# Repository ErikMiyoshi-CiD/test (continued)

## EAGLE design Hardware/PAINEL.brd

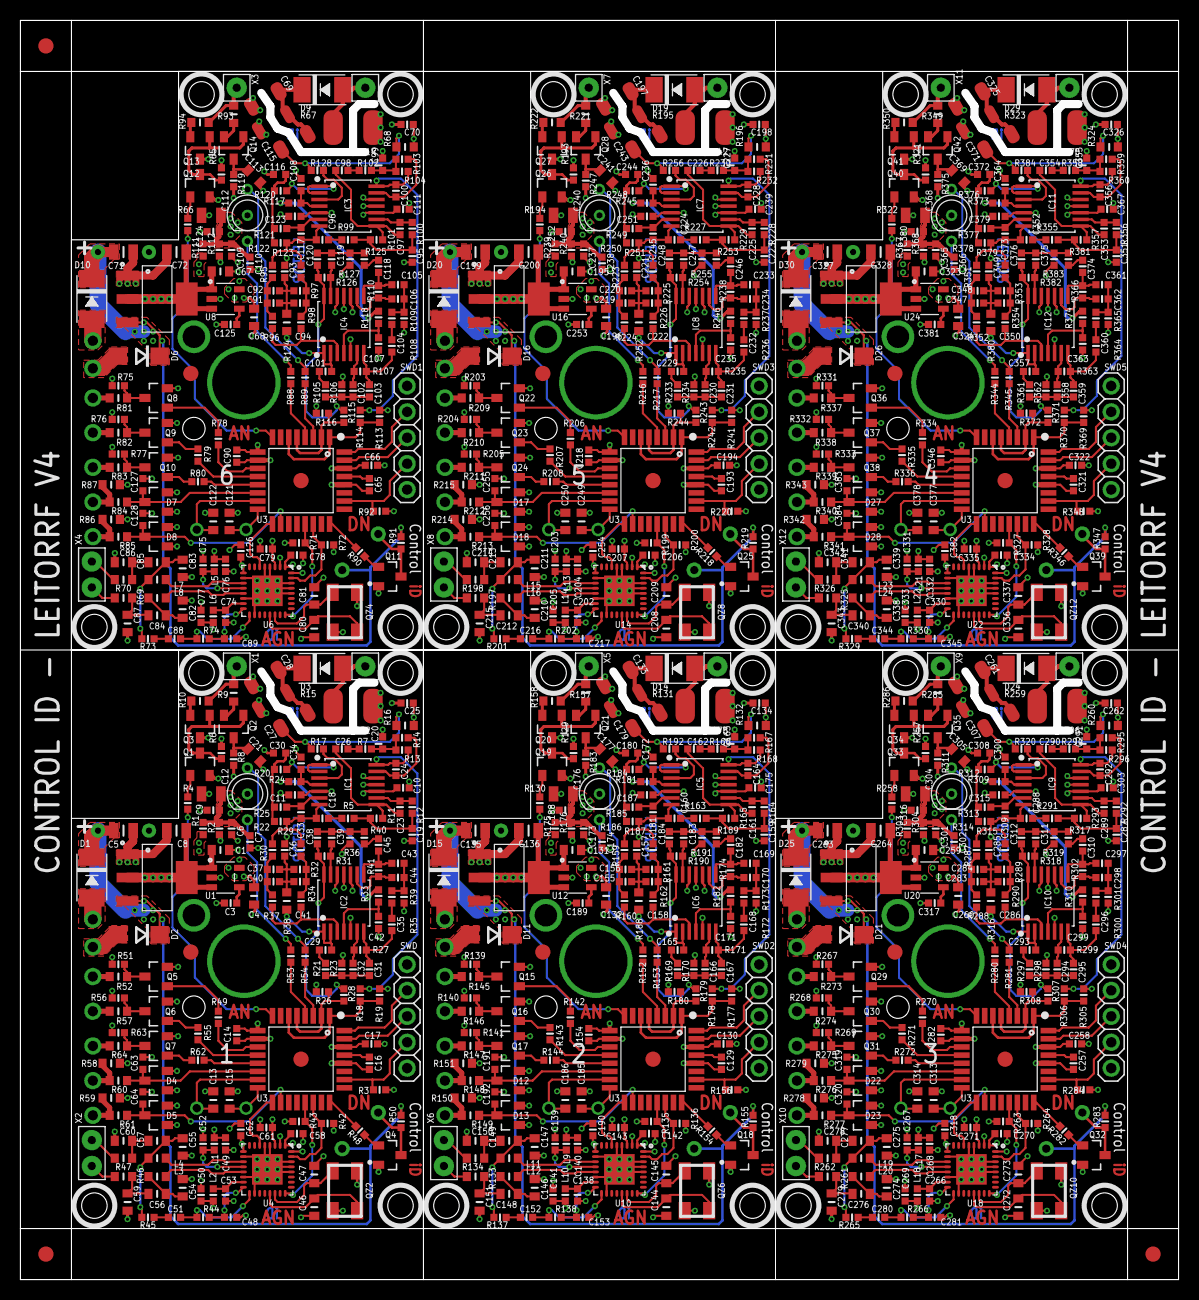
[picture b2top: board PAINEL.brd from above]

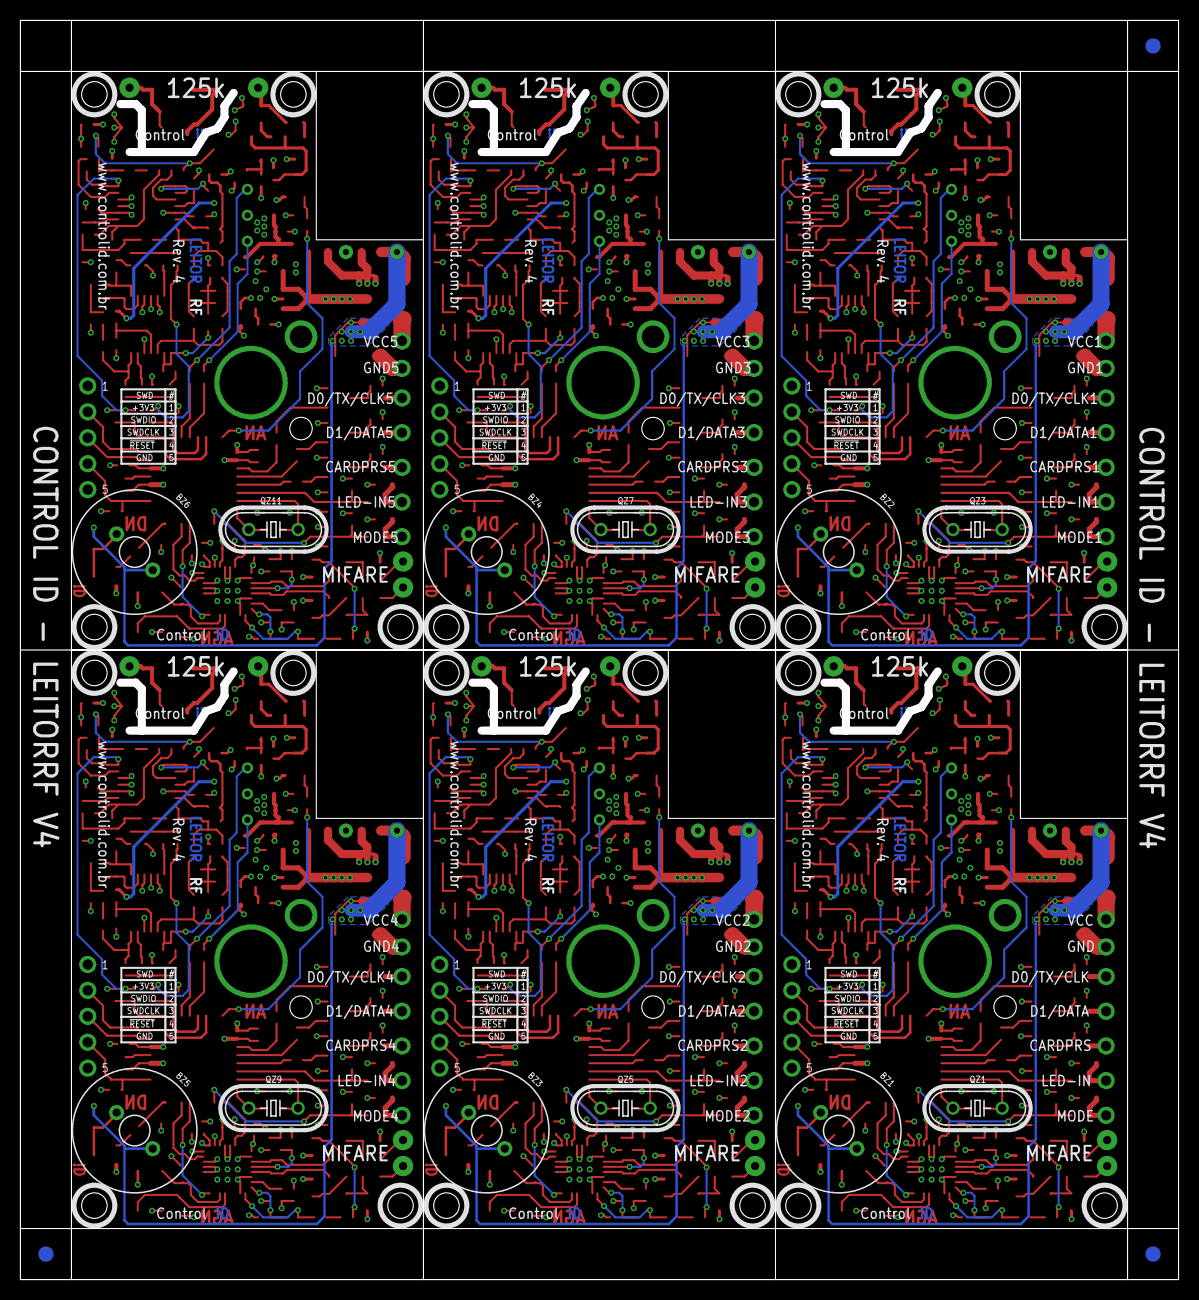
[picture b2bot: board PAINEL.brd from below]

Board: 4 copper layers, 113.5 x 123.4 mm, 1002 parts (15 on the bottom side), 588 nets.

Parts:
BZ1, BZ2, BZ3, BZ4, BZ5, BZ6: F/TMB
C1, C4, C67, C68, C131, C132, C195, C196, C259, C260, C323, C324: 4.7u; C0603
C2, C73, C137, C201, C265, C329: ESK108M016AH2AA
C3, C7, C110, C125, C174, C189, C238, C253, C302, C317, C366, C381: 10n; C0402
C5, C8, C12, C71, C72, C112, C135, C136, C176, C199, C200, C240, C263, C264, C304, C327, C328, C368: 10u; C0805
C6, C9, C10, C11, C14, C16, C17, C25, C34, C42, C48, C52, C53, C58, C61, C62, C63, C64, C65, C66, C70, C74, C75, C78, C79, C89, C90, C107, C108, C109, C111, C123, C124, C126, C127, C128, C129, C130, C134, C138, C139, C142, C143, C153, C154, C171, C172, C173, C175, C187, C188, C190, C191, C192, C193, C194, C198, C202, C203, C206, C207, C217, C218, C235, C236, C237, C239, C251, C252, C254, C255, C256, C257, C258, C262, C266, C267, C270, C271, C281, C282, C299, C300, C301, C303, C315, C316, C318, C319, C320, C321, C322, C326, C330, C331, C334, C335, C345, C346, C363, C364, C365, C367, C379, C380, C382, C383, C384: 0.1u; C0402
C13, C15, C46, C47, C56, C57, C80, C81, C84, C85, C121, C122, C144, C145, C148, C149, C185, C186, C208, C209, C212, C213, C249, C250, C272, C273, C276, C277, C313, C314, C336, C337, C340, C341, C377, C378: 18p; C0603
C18, C26, C96, C98, C160, C162, C224, C226, C288, C290, C352, C354: 220n; C0402
C19, C20, C95, C99, C159, C163, C223, C227, C287, C291, C351, C355: 4.7n; C0402
C21, C113, C177, C241, C305, C369: DNP; C0603
C22, C114, C178, C242, C306, C370: 1n; C1812S
C23, C24, C33, C97, C100, C117, C161, C164, C181, C225, C228, C245, C289, C292, C309, C353, C356, C373: 68p; C0402
C27, C115, C179, C243, C307, C371: 220n; C1206S
C28, C69, C133, C197, C261, C325: 1n; C1206S
C29, C35, C45, C101, C104, C118, C165, C168, C182, C229, C232, C246, C293, C296, C310, C357, C360, C374: F:0.1uP:10n; C0402
C30, C116, C180, C244, C308, C372: 680p; C0402
C31, C38, C43, C103, C105, C120, C167, C169, C184, C231, C233, C248, C295, C297, C312, C359, C361, C376: F:220pP:68p; C0402
C32, C39, C44, C102, C106, C119, C166, C170, C183, C230, C234, C247, C294, C298, C311, C358, C362, C375: F:1nP:100p; C0402
C36, C37, C40, C41, C91, C92, C93, C94, C155, C156, C157, C158, C219, C220, C221, C222, C283, C284, C285, C286, C347, C348, C349, C350: 47p; C0402
C49, C50, C76, C77, C140, C141, C204, C205, C268, C269, C332, C333: 100p; C0402
C51, C88, C152, C216, C280, C344: 1n; C0402
C54, C55, C82, C83, C146, C147, C210, C211, C274, C275, C338, C339: 120p; C0603
C59, C60, C86, C87, C150, C151, C214, C215, C278, C279, C342, C343: 56p; C0603
CARDPRS, CARDPRS1, CARDPRS2, CARDPRS3, CARDPRS4, CARDPRS5: CARD-PRES; HOLE
D0/TX/CLK, D0/TX/CLK1, D0/TX/CLK2, D0/TX/CLK3, D0/TX/CLK4, D0/TX/CLK5: D0/CLK/TX; HOLE
D1, D3, D9, D10, D14, D15, D19, D20, D24, D25, D29, D30: BYG20J; SMA
D1/DATA, D1/DATA1, D1/DATA2, D1/DATA3, D1/DATA4, D1/DATA5: D1/DATA; HOLE
D2, D6, D11, D16, D21, D26: DO214AC
D4, D5, D7, D8, D12, D13, D17, D18, D22, D23, D27, D28: BAT54S; SOT23
FID1, FID2, FID3, FID4, FID5, FID6, FID7, FID8, FID9, FID10, FID11, FID12: FIDUCIAL1.5X3; FIDUCIAL-1.5X3
GND, GND1, GND2, GND3, GND4, GND5: GND; HOLE
IC1, IC2, IC3, IC4, IC5, IC6, IC7, IC8, IC9, IC10, IC11, IC12: TL084; TSSOP14
JP1, JP2, JP3, JP4, JP5, JP6: FIDUCIAL1.5X3; FIDUCIAL-1.5X3
L1, L2, L5, L6, L9, L10, L13, L14, L17, L18, L21, L22: 22n; R0402
L3, L4, L7, L8, L11, L12, L15, L16, L19, L20, L23, L24: 1u; R0603
LED1, LED2, LED3, LED4, LED5, LED6: LTL1BEKVJNN
LED-IN, LED-IN1, LED-IN2, LED-IN3, LED-IN4, LED-IN5: LED; HOLE
MODE, MODE1, MODE2, MODE3, MODE4, MODE5: MODESELECT; HOLE
Q1, Q12, Q19, Q26, Q33, Q40: DMN3404; SOT23
Q2, Q4, Q5, Q6, Q7, Q8, Q9, Q10, Q11, Q14, Q15, Q16, Q17, Q18, Q21, Q22, Q23, Q24, Q25, Q28, Q29, Q30, Q31, Q32, Q35, Q36, Q37, Q38, Q39, Q42: MMBT4401; SOT23
Q3, Q13, Q20, Q27, Q34, Q41: MMBT4403; SOT23
QZ1, QZ3, QZ5, QZ7, QZ9, QZ11: 8MHz; HC49/S
QZ2, QZ4, QZ6, QZ8, QZ10, QZ12: 27.12MHz; CRISTAL4SMD
R1, R2, R29, R111, R112, R123, R175, R176, R187, R239, R240, R251, R303, R304, R315, R367, R368, R379: 470; R0402
R3, R92, R156, R220, R284, R348: 12k; R0402
R4, R17, R44, R50, R51, R56, R63, R66, R74, R75, R76, R77, R91, R128, R130, R138, R139, R140, R141, R155, R192, R194, R202, R203, R204, R205, R219, R256, R258, R266, R267, R268, R269, R283, R320, R322, R330, R331, R332, R333, R347, R384: 1k; R0402
R5, R7, R42, R43, R71, R72, R99, R102, R135, R136, R163, R166, R199, R200, R227, R230, R263, R264, R291, R294, R327, R328, R355, R358: 4.7k; R0402
R6, R45, R48, R49, R55, R62, R65, R73, R78, R79, R80, R90, R129, R137, R142, R143, R144, R154, R193, R201, R206, R207, R208, R218, R257, R265, R270, R271, R272, R282, R321, R329, R334, R335, R336, R346: 2.2k; R0402
R8, R24, R33, R117, R118, R119, R181, R182, R183, R245, R246, R247, R309, R310, R311, R373, R374, R375: 0; R0402
R9, R10, R93, R94, R157, R158, R221, R222, R285, R286, R349, R350: 10; R0603
R11, R13, R101, R104, R165, R168, R229, R232, R293, R296, R357, R360: 91k; R0402
R12, R14, R25, R100, R103, R121, R164, R167, R185, R228, R231, R249, R292, R295, R313, R356, R359, R377: 13k; R0402
R15, R67, R131, R195, R259, R323: 1M; R1206S
R16, R58, R59, R60, R61, R68, R84, R85, R86, R87, R132, R148, R149, R150, R151, R196, R212, R213, R214, R215, R260, R276, R277, R278, R279, R324, R340, R341, R342, R343: 100k; R0603
R18, R28, R30, R32, R34, R37, R95, R96, R97, R98, R114, R115, R159, R160, R161, R162, R178, R179, R223, R224, R225, R226, R242, R243, R287, R288, R289, R290, R306, R307, R351, R352, R353, R354, R370, R371: 27k; R0402
R19, R20, R22, R26, R113, R116, R120, R122, R177, R180, R184, R186, R241, R244, R248, R250, R305, R308, R312, R314, R369, R372, R376, R378: 9.1k; R0402
R21, R35, R40, R105, R108, R125, R169, R172, R189, R233, R236, R253, R297, R300, R317, R361, R364, R381: F:5.1kP:5.6k; R0402
R23, R36, R39, R106, R109, R127, R170, R173, R191, R234, R237, R255, R298, R301, R319, R362, R365, R383: F:7.5kP:5.1k; R0402
R27, R31, R41, R107, R110, R126, R171, R174, R190, R235, R238, R254, R299, R302, R318, R363, R366, R382: F:180kP:270k; R0402
R38, R52, R57, R64, R81, R82, R83, R124, R145, R146, R147, R188, R209, R210, R211, R252, R273, R274, R275, R316, R337, R338, R339, R380: 100; R0603
R46, R47, R69, R70, R133, R134, R197, R198, R261, R262, R325, R326: 3.3; R0603
R53, R88, R152, R216, R280, R344: 130; R0402
R54, R89, R153, R217, R281, R345: 120; R0402
SWD, SWD1, SWD2, SWD3, SWD4, SWD5: 1X05
U1, U8, U12, U16, U20, U24: TLV71333PDBVR; SOT-23-5
U2, U5, U9, U13, U17, U21: NCP1117LPST50T3G; SOT223-3L
U3, U7, U11, U15, U19, U23: SAMD20E14A-AUT; TQFP32
U4, U6, U10, U14, U18, U22: MFRC52202HN1; QFN32
VCC, VCC1, VCC2, VCC3, VCC4, VCC5: VCC; HOLE
X1, X3, X5, X7, X9, X11: ANTENA; 22-23-2021
X2, X4, X6, X8, X10, X12: MIFARE; ANTENNA

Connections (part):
125KHZ: R4.1, U3.8
125KHZ1: R66.1, U7.8
125KHZ2: R130.1, U11.8
125KHZ3: R194.1, U15.8
125KHZ4: R258.1, U19.8
125KHZ5: R322.1, U23.8
+3V1: C66.1, C68.1, C76.1, C77.1, C78.1, C79.1, C90.1, C126.1, D7.2, D8.2, L5.1, L6.1, R71.2, R72.2, R86.1, R87.1, R92.2, SWD1.1, U6.1, U6.2, U6.3, U6.9, U7.9, U7.30, U8.5
+3V2: C130.1, C132.1, C140.1, C141.1, C142.1, C143.1, C154.1, C190.1, D12.2, D13.2, L9.1, L10.1, R135.2, R136.2, R150.1, R151.1, R156.2, SWD2.1, U10.1, U10.2, U10.3, U10.9, U11.9, U11.30, U12.5
+3V3: C4.1, C14.1, C17.1, C49.1, C50.1, C58.1, C61.1, C62.1, D4.2, D5.2, L1.1, L2.1, R3.2, R42.2, R43.2, R58.1, R59.1, SWD.1, U1.5, U3.9, U3.30, U4.1, U4.2, U4.3, U4.9
+3V4: C194.1, C196.1, C204.1, C205.1, C206.1, C207.1, C218.1, C254.1, D17.2, D18.2, L13.1, L14.1, R199.2, R200.2, R214.1, R215.1, R220.2, SWD3.1, U14.1, U14.2, U14.3, U14.9, U15.9, U15.30, U16.5
+3V5: C258.1, C260.1, C268.1, C269.1, C270.1, C271.1, C282.1, C318.1, D22.2, D23.2, L17.1, L18.1, R263.2, R264.2, R278.1, R279.1, R284.2, SWD4.1, U18.1, U18.2, U18.3, U18.9, U19.9, U19.30, U20.5
+3V6: C322.1, C324.1, C332.1, C333.1, C334.1, C335.1, C346.1, C382.1, D27.2, D28.2, L21.1, L22.1, R327.2, R328.2, R342.1, R343.1, R348.2, SWD5.1, U22.1, U22.2, U22.3, U22.9, U23.9, U23.30, U24.5
+5V: C1.1, C8.1, R51.2, R56.2, R63.2, U1.1, U1.3, U2.2, U2.4
+5V1: C67.1, C72.1, R75.2, R76.2, R77.2, U5.2, U5.4, U8.1, U8.3
+5V2: C131.1, C136.1, R139.2, R140.2, R141.2, U9.2, U9.4, U12.1, U12.3
+5V3: C195.1, C200.1, R203.2, R204.2, R205.2, U13.2, U13.4, U16.1, U16.3
+5V4: C259.1, C264.1, R267.2, R268.2, R269.2, U17.2, U17.4, U20.1, U20.3
+5V5: C323.1, C328.1, R331.2, R332.2, R333.2, U21.2, U21.4, U24.1, U24.3
+12V: BZ1.+, C2.+, C5.1, D1.K, D2.C, R1.1, R6.2, R8.2, R24.1, R33.1, R50.2, U2.3
+12V1: BZ2.+, C71.1, C73.+, D6.C, D10.K, R65.2, R91.2, R111.1, R117.1, R118.1, R119.2, U5.3
+12V2: BZ3.+, C135.1, C137.+, D11.C, D15.K, R129.2, R155.2, R175.1, R181.1, R182.1, R183.2, U9.3
+12V3: BZ4.+, C199.1, C201.+, D16.C, D20.K, R193.2, R219.2, R239.1, R245.1, R246.1, R247.2, U13.3
+12V4: BZ5.+, C263.1, C265.+, D21.C, D25.K, R257.2, R283.2, R303.1, R309.1, R310.1, R311.2, U17.3
+12V5: BZ6.+, C327.1, C329.+, D26.C, D30.K, R321.2, R347.2, R367.1, R373.1, R374.1, R375.2, U21.3
ASK: R18.2, R19.2, U3.1, U3.6
ASK1: R113.2, R114.2, U7.1, U7.6
ASK2: R177.2, R178.2, U11.1, U11.6
ASK3: R241.2, R242.2, U15.1, U15.6
ASK4: R305.2, R306.2, U19.1, U19.6
ASK5: R369.2, R370.2, U23.1, U23.6
ASK-OUT: C18.2, C33.1, C36.2, IC1.7, R22.1, R30.1
ASK-OUT1: C93.2, C96.2, C117.1, IC3.7, R95.1, R122.1
ASK-OUT2: C157.2, C160.2, C181.1, IC5.7, R159.1, R186.1
ASK-OUT3: C221.2, C224.2, C245.1, IC7.7, R223.1, R250.1
ASK-OUT4: C285.2, C288.2, C309.1, IC9.7, R287.1, R314.1
ASK-OUT5: C349.2, C352.2, C373.1, IC11.7, R351.1, R378.1
ASK_MID: C26.2, R7.1
ASK_MID1: C98.2, R102.1
ASK_MID2: C162.2, R166.1
ASK_MID3: C226.2, R230.1
ASK_MID4: C290.2, R294.1
ASK_MID5: C354.2, R358.1
BUZZER: R48.2, U3.24
BUZZER1: R90.2, U7.24
BUZZER2: R154.2, U11.24
BUZZER3: R218.2, U15.24
BUZZER4: R282.2, U19.24
BUZZER5: R346.2, U23.24
CARD-PRES: R62.2, U3.13
CARD-PRES1: R80.2, U7.13
CARD-PRES2: R144.2, U11.13
CARD-PRES3: R208.2, U15.13
CARD-PRES4: R272.2, U19.13
CARD-PRES5: R336.2, U23.13
D0/TX/CLK: R49.2, U3.11
D0/TX/CLK1: R78.2, U7.11
D0/TX/CLK2: R142.2, U11.11
D0/TX/CLK3: R206.2, U15.11
D0/TX/CLK4: R270.2, U19.11
D0/TX/CLK5: R334.2, U23.11
D1/DATA: R55.2, U3.12
D1/DATA1: R79.2, U7.12
D1/DATA2: R143.2, U11.12
D1/DATA3: R207.2, U15.12
D1/DATA4: R271.2, U19.12
D1/DATA5: R335.2, U23.12
FSK-PSK: R26.2, R28.2, U3.2, U3.5
FSK-PSK1: R115.2, R116.2, U7.2, U7.5
FSK-PSK2: R179.2, R180.2, U11.2, U11.5
FSK-PSK3: R243.2, R244.2, U15.2, U15.5
FSK-PSK4: R307.2, R308.2, U19.2, U19.5
FSK-PSK5: R371.2, R372.2, U23.2, U23.5
FSK/PSK: C29.2, IC2.1, IC2.2, R38.1
FSK/PSK1: C101.2, IC4.1, IC4.2, R124.1
FSK/PSK2: C165.2, IC6.1, IC6.2, R188.1
FSK/PSK3: C229.2, IC8.1, IC8.2, R252.1
FSK/PSK4: C293.2, IC10.1, IC10.2, R316.1
FSK/PSK5: C357.2, IC12.1, IC12.2, R380.1
GND: C1.2, C2.-, C3.2, C4.2, C5.2, C6.2, C7.2, C8.2, C9.2, C10.2, C11.2, C12.2, C13.2, C14.2, C15.2, C16.2, C17.2, C19.2, C20.2, C21.2, C22.2, C25.2, C28.2, C30.2, C34.2, C42.2, C46.2, C47.2, C48.2, C49.2, C50.2, C52.2, C53.2, C54.2, C55.1, C58.2, C59.2, C60.1, C61.2, C62.2, C63.2, C64.2, D2.A, D4.1, D5.1, GND.P$1, IC1.11, IC2.11, LED1.COMMON, Q1.2, Q3.3, Q4.2, Q5.2, Q6.2, Q7.2, QZ2.2, QZ2.4, R2.1, R15.1, R19.1, R26.1, SWD.5, U1.2, U2.1, U3.10, U3.28, U4.4, U4.5, U4.10, U4.14, U4.18, U4.28, U4.29, U4.30, U4.32, U4.33
GND1: C65.2, C66.2, C67.2, C68.2, C69.2, C70.2, C71.2, C72.2, C73.-, C74.2, C75.2, C76.2, C77.2, C78.2, C79.2, C80.2, C81.2, C82.2, C83.1, C86.1, C87.2, C89.2, C90.2, C95.2, C99.2, C107.2, C108.2, C109.2, C110.2, C111.2, C112.2, C113.2, C114.2, C116.2, C121.2, C122.2, C123.2, C124.2, C125.2, C126.2, C127.2, C128.2, D6.A, D7.1, D8.1, GND1.P$1, IC3.11, IC4.11, LED2.COMMON, Q8.2, Q9.2, Q10.2, Q11.2, Q12.2, Q13.3, QZ4.2, QZ4.4, R67.1, R112.1, R113.1, R116.1, SWD1.5, U5.1, U6.4, U6.5, U6.10, U6.14, U6.18, U6.28, U6.29, U6.30, U6.32, U6.33, U7.10, U7.28, U8.2
GND2: C129.2, C130.2, C131.2, C132.2, C133.2, C134.2, C135.2, C136.2, C137.-, C138.2, C139.2, C140.2, C141.2, C142.2, C143.2, C144.2, C145.2, C146.2, C147.1, C150.1, C151.2, C153.2, C154.2, C159.2, C163.2, C171.2, C172.2, C173.2, C174.2, C175.2, C176.2, C177.2, C178.2, C180.2, C185.2, C186.2, C187.2, C188.2, C189.2, C190.2, C191.2, C192.2, D11.A, D12.1, D13.1, GND2.P$1, IC5.11, IC6.11, LED3.COMMON, Q15.2, Q16.2, Q17.2, Q18.2, Q19.2, Q20.3, QZ6.2, QZ6.4, R131.1, R176.1, R177.1, R180.1, SWD2.5, U9.1, U10.4, U10.5, U10.10, U10.14, U10.18, U10.28, U10.29, U10.30, U10.32, U10.33, U11.10, U11.28, U12.2
GND3: C193.2, C194.2, C195.2, C196.2, C197.2, C198.2, C199.2, C200.2, C201.-, C202.2, C203.2, C204.2, C205.2, C206.2, C207.2, C208.2, C209.2, C210.2, C211.1, C214.1, C215.2, C217.2, C218.2, C223.2, C227.2, C235.2, C236.2, C237.2, C238.2, C239.2, C240.2, C241.2, C242.2, C244.2, C249.2, C250.2, C251.2, C252.2, C253.2, C254.2, C255.2, C256.2, D16.A, D17.1, D18.1, GND3.P$1, IC7.11, IC8.11, LED4.COMMON, Q22.2, Q23.2, Q24.2, Q25.2, Q26.2, Q27.3, QZ8.2, QZ8.4, R195.1, R240.1, R241.1, R244.1, SWD3.5, U13.1, U14.4, U14.5, U14.10, U14.14, U14.18, U14.28, U14.29, U14.30, U14.32, U14.33, U15.10, U15.28, U16.2
GND4: C257.2, C258.2, C259.2, C260.2, C261.2, C262.2, C263.2, C264.2, C265.-, C266.2, C267.2, C268.2, C269.2, C270.2, C271.2, C272.2, C273.2, C274.2, C275.1, C278.1, C279.2, C281.2, C282.2, C287.2, C291.2, C299.2, C300.2, C301.2, C302.2, C303.2, C304.2, C305.2, C306.2, C308.2, C313.2, C314.2, C315.2, C316.2, C317.2, C318.2, C319.2, C320.2, D21.A, D22.1, D23.1, GND4.P$1, IC9.11, IC10.11, LED5.COMMON, Q29.2, Q30.2, Q31.2, Q32.2, Q33.2, Q34.3, QZ10.2, QZ10.4, R259.1, R304.1, R305.1, R308.1, SWD4.5, U17.1, U18.4, U18.5, U18.10, U18.14, U18.18, U18.28, U18.29, U18.30, U18.32, U18.33, U19.10, U19.28, U20.2
GND5: C321.2, C322.2, C323.2, C324.2, C325.2, C326.2, C327.2, C328.2, C329.-, C330.2, C331.2, C332.2, C333.2, C334.2, C335.2, C336.2, C337.2, C338.2, C339.1, C342.1, C343.2, C345.2, C346.2, C351.2, C355.2, C363.2, C364.2, C365.2, C366.2, C367.2, C368.2, C369.2, C370.2, C372.2, C377.2, C378.2, C379.2, C380.2, C381.2, C382.2, C383.2, C384.2, D26.A, D27.1, D28.1, GND5.P$1, IC11.11, IC12.11, LED6.COMMON, Q36.2, Q37.2, Q38.2, Q39.2, Q40.2, Q41.3, QZ12.2, QZ12.4, R323.1, R368.1, R369.1, R372.1, SWD5.5, U21.1, U22.4, U22.5, U22.10, U22.14, U22.18, U22.28, U22.29, U22.30, U22.32, U22.33, U23.10, U23.28, U24.2
LED-GRN-CTRL: R53.1, U3.4
LED-GRN-CTRL1: R88.1, U7.4
LED-GRN-CTRL2: R152.1, U11.4
LED-GRN-CTRL3: R216.1, U15.4
LED-GRN-CTRL4: R280.1, U19.4
LED-GRN-CTRL5: R344.1, U23.4
LED-INPUT: C63.1, D4.3, R60.1, U3.14
LED-INPUT1: C127.1, D7.3, R84.1, U7.14
LED-INPUT2: C191.1, D12.3, R148.1, U11.14
LED-INPUT3: C255.1, D17.3, R212.1, U15.14
LED-INPUT4: C319.1, D22.3, R276.1, U19.14
LED-INPUT5: C383.1, D27.3, R340.1, U23.14
LED-RED-CTRL: R54.2, U3.3
LED-RED-CTRL1: R89.2, U7.3
LED-RED-CTRL2: R153.2, U11.3
LED-RED-CTRL3: R217.2, U15.3
LED-RED-CTRL4: R281.2, U19.3
LED-RED-CTRL5: R345.2, U23.3
MIFARE-RST: U3.17, U4.6
MIFARE-RST1: U6.6, U7.17
MIFARE-RST2: U10.6, U11.17
MIFARE-RST3: U14.6, U15.17
MIFARE-RST4: U18.6, U19.17
MIFARE-RST5: U22.6, U23.17
MIFARE-RX: C51.2, R44.1, U4.17
MIFARE-RX1: C88.2, R74.1, U6.17
MIFARE-RX2: C152.2, R138.1, U10.17
MIFARE-RX3: C216.2, R202.1, U14.17
MIFARE-RX4: C280.2, R266.1, U18.17
MIFARE-RX5: C344.2, R330.1, U22.17
MIFARE-SCL: R42.1, U3.22, U4.31
MIFARE-SCL1: R72.1, U6.31, U7.22
MIFARE-SCL2: R136.1, U10.31, U11.22
MIFARE-SCL3: R200.1, U14.31, U15.22
MIFARE-SCL4: R264.1, U18.31, U19.22
MIFARE-SCL5: R328.1, U22.31, U23.22
MIFARE-SDA: R43.1, U3.21, U4.24
MIFARE-SDA1: R71.1, U6.24, U7.21
MIFARE-SDA2: R135.1, U10.24, U11.21
MIFARE-SDA3: R199.1, U14.24, U15.21
MIFARE-SDA4: R263.1, U18.24, U19.21
MIFARE-SDA5: R327.1, U22.24, U23.21
MIFARE-TX1: L4.1, U4.11
MIFARE-TX2: L3.1, U4.13
MIFARE-TX3: L7.1, U6.11
MIFARE-TX4: L8.1, U6.13
MIFARE-TX5: L11.1, U10.11
MIFARE-TX6: L12.1, U10.13
MIFARE-TX7: L15.1, U14.11
MIFARE-TX8: L16.1, U14.13
MIFARE-TX9: L19.1, U18.11
MIFARE-TX10: L20.1, U18.13
MIFARE-TX11: L23.1, U22.11
MIFARE-TX12: L24.1, U22.13
unnamed: Q12.3, Q13.1, Q14.1, R65.1
unnamed: C52.1, L1.2, U4.12
unnamed: C46.1, QZ2.3, U4.21
unnamed: C53.1, L2.2, U4.15
unnamed: C47.1, QZ2.1, U4.22
unnamed: Q6.1, R55.1
unnamed: Q1.3, Q2.1, Q3.1, R6.1
unnamed: Q1.1, R4.2
unnamed: C22.1, D3.A, X1.2
unnamed: IC1.1, IC1.2, R20.1
unnamed: R9.1, R10.2, X1.1
unnamed: C30.1, R20.2, R22.2, R25.1
unnamed: C27.1, C28.1, D3.K, R15.2
unnamed: C27.2, R16.1, R17.2
unnamed: C33.2, IC1.6, R25.2
unnamed: Q2.2, R9.2
unnamed: C37.2, C40.2, R29.1, R32.2, R34.2, R38.2
unnamed: LED-IN.P$1, R58.2, R60.2
unnamed: C37.1, C40.1, R30.2, R37.1
unnamed: C36.1, C41.2, R32.1, R34.1
unnamed: C18.1, R5.2
unnamed: C19.1, R5.1, R11.2, R12.2
unnamed: C41.1, IC2.3, R37.2
unnamed: C38.1, IC2.14, R28.1, R31.1
unnamed: C35.2, R35.2
unnamed: C39.1, IC2.13, R31.2
unnamed: C23.2, IC1.9, R12.1
unnamed: C31.2, C32.2, R21.2, R23.2
unnamed: C38.2, C39.2, R36.2, R40.2
unnamed: C45.1, R40.1
unnamed: C55.2, C57.2, L4.2, R45.1
unnamed: Q5.1, R49.1
unnamed: C57.1, C60.2, R47.1
unnamed: C54.1, C56.2, L3.2
unnamed: C56.1, C59.1, R46.1
unnamed: C51.1, R45.2
unnamed: C48.1, R44.2, U4.16
unnamed: R46.2, X2.1
unnamed: R47.2, X2.2
unnamed: C43.1, C45.2, IC2.8, R41.1
unnamed: Q6.3, R56.1, R57.2
unnamed: Q7.3, R63.1, R64.2
unnamed: MODE.P$1, R59.2, R61.2
unnamed: Q7.1, R62.1
unnamed: Q5.3, R51.1, R52.2
unnamed: D0/TX/CLK.P$1, R52.1
unnamed: C16.1, U3.29
unnamed: C21.1, Q2.3, R8.1
unnamed: C34.1, IC1.4, R24.2
unnamed: D1/DATA.P$1, R57.1
unnamed: CARDPRS.P$1, R64.1
unnamed: LED1.ANODE_RED, R53.2
unnamed: LED1.ANODE_GRN, R54.1
unnamed: BZ1.-, Q4.3, R50.1
unnamed: Q4.1, R48.1
unnamed: C23.1, C26.1, IC1.8, R11.1
unnamed: C42.1, IC2.4, R33.2
unnamed: IC1.3, R17.1
unnamed: Q12.1, R66.2
unnamed: Q3.2, R10.1
unnamed: R93.1, R94.2, X3.1
unnamed: C114.1, D9.A, X3.2
unnamed: C20.1, R7.2, R13.1, R14.2
unnamed: C24.1, IC1.13, R14.1
unnamed: C3.1, U1.4
unnamed: C69.1, C115.1, D9.K, R67.2
unnamed: C75.1, L5.2, U6.12
unnamed: C74.1, L6.2, U6.15
unnamed: C29.1, R21.1
unnamed: C80.1, QZ4.3, U6.21
unnamed: C31.1, C35.1, IC2.7, R27.2
unnamed: C32.1, IC2.6, R27.1
unnamed: C81.1, QZ4.1, U6.22
unnamed: C43.2, C44.2, R35.1, R39.2
unnamed: C44.1, IC2.9, R41.2
unnamed: C83.2, C85.2, L7.2, R73.1
unnamed: C85.1, C86.2, R70.1
unnamed: C82.1, C84.2, L8.2
unnamed: C84.1, C87.1, R69.1
unnamed: C88.1, R73.2
unnamed: C89.1, R74.2, U6.16
unnamed: R69.2, X4.1
unnamed: R70.2, X4.2
unnamed: Q9.1, R79.1
unnamed: Q8.1, R78.1
unnamed: Q9.3, R76.1, R82.2
unnamed: Q10.3, R77.1, R83.2
unnamed: Q10.1, R80.1
unnamed: Q8.3, R75.1, R81.2
unnamed: C24.2, IC1.14, R13.2, R18.1
unnamed: D0/TX/CLK1.P$1, R81.1
unnamed: D1/DATA1.P$1, R82.1
unnamed: CARDPRS1.P$1, R83.1
unnamed: BZ2.-, Q11.3, R91.1
unnamed: Q11.1, R90.1
unnamed: LED-IN1.P$1, R84.2, R87.2
unnamed: MODE1.P$1, R85.2, R86.2
unnamed: C65.1, U7.29
unnamed: Q13.2, R94.1
unnamed: C91.1, C92.1, R95.2, R96.1
unnamed: C93.1, C94.2, R97.1, R98.1
unnamed: C94.1, IC4.3, R96.2
unnamed: C97.2, IC3.9, R100.1
unnamed: C99.1, R102.2, R103.2, R104.1
unnamed: C100.1, IC3.13, R103.1
unnamed: C101.1, R105.1
unnamed: C103.1, C104.1, IC4.7, R107.2
unnamed: C102.1, IC4.6, R107.1
unnamed: C105.2, C106.2, R108.1, R109.2
unnamed: C106.1, IC4.9, R110.2
unnamed: C105.1, C118.2, IC4.8, R110.1
unnamed: C100.2, IC3.14, R104.2, R114.1
unnamed: C108.1, IC3.4, R117.2
unnamed: C107.1, IC4.4, R118.2
unnamed: C113.1, Q14.3, R119.1
unnamed: C115.2, R68.1, R128.2
unnamed: IC3.1, IC3.2, R120.1
unnamed: C116.1, R120.2, R121.1, R122.2
unnamed: C117.2, IC3.6, R121.2
unnamed: Q14.2, R93.2
unnamed: C91.2, C92.2, R97.2, R98.2, R123.1, R124.2
unnamed: C96.1, R99.2
unnamed: C95.1, R99.1, R100.2, R101.2
unnamed: C120.1, IC4.14, R115.1, R126.1
unnamed: C104.2, R108.2
unnamed: C119.1, IC4.13, R126.2
unnamed: C119.2, C120.2, R125.2, R127.2
unnamed: C118.1, R125.1
unnamed: C97.1, C98.1, IC3.8, R101.1
unnamed: C102.2, C103.2, R105.2, R106.2
unnamed: IC3.3, R128.1
unnamed: LED2.ANODE_RED, R88.2
unnamed: LED2.ANODE_GRN, R89.1
unnamed: C125.1, U8.4
unnamed: Q19.3, Q20.1, Q21.1, R129.1
unnamed: Q19.1, R130.2
unnamed: R157.1, R158.2, X5.1
unnamed: C178.1, D14.A, X5.2
unnamed: C133.1, C179.1, D14.K, R131.2
unnamed: C139.1, L9.2, U10.12
unnamed: C138.1, L10.2, U10.15
unnamed: C144.1, QZ6.3, U10.21
unnamed: C145.1, QZ6.1, U10.22
unnamed: C147.2, C149.2, L11.2, R137.1
unnamed: C149.1, C150.2, R134.1
unnamed: C146.1, C148.2, L12.2
unnamed: C148.1, C151.1, R133.1
unnamed: C152.1, R137.2
unnamed: C153.1, R138.2, U10.16
unnamed: R133.2, X6.1
unnamed: R134.2, X6.2
unnamed: Q16.1, R143.1
unnamed: Q15.1, R142.1
unnamed: Q16.3, R140.1, R146.2
unnamed: Q17.3, R141.1, R147.2
unnamed: Q17.1, R144.1
unnamed: Q15.3, R139.1, R145.2
unnamed: D0/TX/CLK2.P$1, R145.1
unnamed: D1/DATA2.P$1, R146.1
unnamed: CARDPRS2.P$1, R147.1
unnamed: BZ3.-, Q18.3, R155.1
unnamed: Q18.1, R154.1
unnamed: LED-IN2.P$1, R148.2, R151.2
unnamed: MODE2.P$1, R149.2, R150.2
unnamed: C129.1, U11.29
unnamed: Q20.2, R158.1
unnamed: C155.1, C156.1, R159.2, R160.1
unnamed: C157.1, C158.2, R161.1, R162.1
unnamed: C158.1, IC6.3, R160.2
unnamed: C161.2, IC5.9, R164.1
unnamed: C163.1, R166.2, R167.2, R168.1
unnamed: C164.1, IC5.13, R167.1
unnamed: C165.1, R169.1
unnamed: C167.1, C168.1, IC6.7, R171.2
unnamed: C166.1, IC6.6, R171.1
unnamed: C169.2, C170.2, R172.1, R173.2
unnamed: C170.1, IC6.9, R174.2
unnamed: C169.1, C182.2, IC6.8, R174.1
unnamed: C164.2, IC5.14, R168.2, R178.1
unnamed: C172.1, IC5.4, R181.2
unnamed: C171.1, IC6.4, R182.2
unnamed: C177.1, Q21.3, R183.1
unnamed: C179.2, R132.1, R192.2
unnamed: IC5.1, IC5.2, R184.1
unnamed: C180.1, R184.2, R185.1, R186.2
unnamed: C181.2, IC5.6, R185.2
unnamed: Q21.2, R157.2
unnamed: C155.2, C156.2, R161.2, R162.2, R187.1, R188.2
unnamed: C160.1, R163.2
unnamed: C159.1, R163.1, R164.2, R165.2
unnamed: C184.1, IC6.14, R179.1, R190.1
unnamed: C168.2, R172.2
unnamed: C183.1, IC6.13, R190.2
unnamed: C183.2, C184.2, R189.2, R191.2
unnamed: C182.1, R189.1
unnamed: C161.1, C162.1, IC5.8, R165.1
unnamed: C166.2, C167.2, R169.2, R170.2
unnamed: IC5.3, R192.1
unnamed: LED3.ANODE_RED, R152.2
unnamed: LED3.ANODE_GRN, R153.1
unnamed: C189.1, U12.4
unnamed: Q26.3, Q27.1, Q28.1, R193.1
unnamed: Q26.1, R194.2
unnamed: R221.1, R222.2, X7.1
unnamed: C242.1, D19.A, X7.2
unnamed: C197.1, C243.1, D19.K, R195.2
unnamed: C203.1, L13.2, U14.12
unnamed: C202.1, L14.2, U14.15
unnamed: C208.1, QZ8.3, U14.21
unnamed: C209.1, QZ8.1, U14.22
unnamed: C211.2, C213.2, L15.2, R201.1
unnamed: C213.1, C214.2, R198.1
unnamed: C210.1, C212.2, L16.2
unnamed: C212.1, C215.1, R197.1
unnamed: C216.1, R201.2
unnamed: C217.1, R202.2, U14.16
unnamed: R197.2, X8.1
unnamed: R198.2, X8.2
unnamed: Q23.1, R207.1
unnamed: Q22.1, R206.1
unnamed: Q23.3, R204.1, R210.2
unnamed: Q24.3, R205.1, R211.2
unnamed: Q24.1, R208.1
unnamed: Q22.3, R203.1, R209.2
unnamed: D0/TX/CLK3.P$1, R209.1
unnamed: D1/DATA3.P$1, R210.1
unnamed: CARDPRS3.P$1, R211.1
unnamed: BZ4.-, Q25.3, R219.1
unnamed: Q25.1, R218.1
unnamed: LED-IN3.P$1, R212.2, R215.2
unnamed: MODE3.P$1, R213.2, R214.2
unnamed: C193.1, U15.29
unnamed: Q27.2, R222.1
unnamed: C219.1, C220.1, R223.2, R224.1
unnamed: C221.1, C222.2, R225.1, R226.1
unnamed: C222.1, IC8.3, R224.2
unnamed: C225.2, IC7.9, R228.1
unnamed: C227.1, R230.2, R231.2, R232.1
unnamed: C228.1, IC7.13, R231.1
unnamed: C229.1, R233.1
unnamed: C231.1, C232.1, IC8.7, R235.2
unnamed: C230.1, IC8.6, R235.1
unnamed: C233.2, C234.2, R236.1, R237.2
unnamed: C234.1, IC8.9, R238.2
unnamed: C233.1, C246.2, IC8.8, R238.1
unnamed: C228.2, IC7.14, R232.2, R242.1
unnamed: C236.1, IC7.4, R245.2
unnamed: C235.1, IC8.4, R246.2
unnamed: C241.1, Q28.3, R247.1
unnamed: C243.2, R196.1, R256.2
unnamed: IC7.1, IC7.2, R248.1
unnamed: C244.1, R248.2, R249.1, R250.2
unnamed: C245.2, IC7.6, R249.2
unnamed: Q28.2, R221.2
unnamed: C219.2, C220.2, R225.2, R226.2, R251.1, R252.2
unnamed: C224.1, R227.2
unnamed: C223.1, R227.1, R228.2, R229.2
unnamed: C248.1, IC8.14, R243.1, R254.1
unnamed: C232.2, R236.2
unnamed: C247.1, IC8.13, R254.2
unnamed: C247.2, C248.2, R253.2, R255.2
unnamed: C246.1, R253.1
unnamed: C225.1, C226.1, IC7.8, R229.1
unnamed: C230.2, C231.2, R233.2, R234.2
unnamed: IC7.3, R256.1
unnamed: LED4.ANODE_RED, R216.2
unnamed: LED4.ANODE_GRN, R217.1
unnamed: C253.1, U16.4
unnamed: Q33.3, Q34.1, Q35.1, R257.1
unnamed: Q33.1, R258.2
unnamed: R285.1, R286.2, X9.1
unnamed: C306.1, D24.A, X9.2
unnamed: C261.1, C307.1, D24.K, R259.2
unnamed: C267.1, L17.2, U18.12
unnamed: C266.1, L18.2, U18.15
unnamed: C272.1, QZ10.3, U18.21
unnamed: C273.1, QZ10.1, U18.22
unnamed: C275.2, C277.2, L19.2, R265.1
unnamed: C277.1, C278.2, R262.1
unnamed: C274.1, C276.2, L20.2
unnamed: C276.1, C279.1, R261.1
unnamed: C280.1, R265.2
unnamed: C281.1, R266.2, U18.16
unnamed: R261.2, X10.1
unnamed: R262.2, X10.2
unnamed: Q30.1, R271.1
unnamed: Q29.1, R270.1
unnamed: Q30.3, R268.1, R274.2
unnamed: Q31.3, R269.1, R275.2
unnamed: Q31.1, R272.1
unnamed: Q29.3, R267.1, R273.2
unnamed: D0/TX/CLK4.P$1, R273.1
unnamed: D1/DATA4.P$1, R274.1
unnamed: CARDPRS4.P$1, R275.1
unnamed: BZ5.-, Q32.3, R283.1
unnamed: Q32.1, R282.1
unnamed: LED-IN4.P$1, R276.2, R279.2
unnamed: MODE4.P$1, R277.2, R278.2
unnamed: C257.1, U19.29
unnamed: Q34.2, R286.1
unnamed: C283.1, C284.1, R287.2, R288.1
unnamed: C285.1, C286.2, R289.1, R290.1
unnamed: C286.1, IC10.3, R288.2
unnamed: C289.2, IC9.9, R292.1
unnamed: C291.1, R294.2, R295.2, R296.1
unnamed: C292.1, IC9.13, R295.1
unnamed: C293.1, R297.1
unnamed: C295.1, C296.1, IC10.7, R299.2
unnamed: C294.1, IC10.6, R299.1
unnamed: C297.2, C298.2, R300.1, R301.2
unnamed: C298.1, IC10.9, R302.2
unnamed: C297.1, C310.2, IC10.8, R302.1
unnamed: C292.2, IC9.14, R296.2, R306.1
unnamed: C300.1, IC9.4, R309.2
unnamed: C299.1, IC10.4, R310.2
unnamed: C305.1, Q35.3, R311.1
unnamed: C307.2, R260.1, R320.2
unnamed: IC9.1, IC9.2, R312.1
unnamed: C308.1, R312.2, R313.1, R314.2
unnamed: C309.2, IC9.6, R313.2
unnamed: Q35.2, R285.2
unnamed: C283.2, C284.2, R289.2, R290.2, R315.1, R316.2
unnamed: C288.1, R291.2
unnamed: C287.1, R291.1, R292.2, R293.2
unnamed: C312.1, IC10.14, R307.1, R318.1
unnamed: C296.2, R300.2
unnamed: C311.1, IC10.13, R318.2
unnamed: C311.2, C312.2, R317.2, R319.2
unnamed: C310.1, R317.1
unnamed: C289.1, C290.1, IC9.8, R293.1
unnamed: C294.2, C295.2, R297.2, R298.2
unnamed: IC9.3, R320.1
unnamed: LED5.ANODE_RED, R280.2
unnamed: LED5.ANODE_GRN, R281.1
unnamed: C317.1, U20.4
unnamed: Q40.3, Q41.1, Q42.1, R321.1
unnamed: Q40.1, R322.2
unnamed: R349.1, R350.2, X11.1
unnamed: C370.1, D29.A, X11.2
unnamed: C325.1, C371.1, D29.K, R323.2
unnamed: C331.1, L21.2, U22.12
unnamed: C330.1, L22.2, U22.15
unnamed: C336.1, QZ12.3, U22.21
unnamed: C337.1, QZ12.1, U22.22
unnamed: C339.2, C341.2, L23.2, R329.1
unnamed: C341.1, C342.2, R326.1
unnamed: C338.1, C340.2, L24.2
unnamed: C340.1, C343.1, R325.1
unnamed: C344.1, R329.2
unnamed: C345.1, R330.2, U22.16
unnamed: R325.2, X12.1
unnamed: R326.2, X12.2
unnamed: Q37.1, R335.1
unnamed: Q36.1, R334.1
unnamed: Q37.3, R332.1, R338.2
unnamed: Q38.3, R333.1, R339.2
unnamed: Q38.1, R336.1
unnamed: Q36.3, R331.1, R337.2
unnamed: D0/TX/CLK5.P$1, R337.1
unnamed: D1/DATA5.P$1, R338.1
unnamed: CARDPRS5.P$1, R339.1
unnamed: BZ6.-, Q39.3, R347.1
unnamed: Q39.1, R346.1
unnamed: LED-IN5.P$1, R340.2, R343.2
unnamed: MODE5.P$1, R341.2, R342.2
unnamed: C321.1, U23.29
unnamed: Q41.2, R350.1
unnamed: C347.1, C348.1, R351.2, R352.1
unnamed: C349.1, C350.2, R353.1, R354.1
unnamed: C350.1, IC12.3, R352.2
unnamed: C353.2, IC11.9, R356.1
unnamed: C355.1, R358.2, R359.2, R360.1
unnamed: C356.1, IC11.13, R359.1
unnamed: C357.1, R361.1
unnamed: C359.1, C360.1, IC12.7, R363.2
unnamed: C358.1, IC12.6, R363.1
unnamed: C361.2, C362.2, R364.1, R365.2
unnamed: C362.1, IC12.9, R366.2
unnamed: C361.1, C374.2, IC12.8, R366.1
unnamed: C356.2, IC11.14, R360.2, R370.1
unnamed: C364.1, IC11.4, R373.2
unnamed: C363.1, IC12.4, R374.2
unnamed: C369.1, Q42.3, R375.1
unnamed: C371.2, R324.1, R384.2
unnamed: IC11.1, IC11.2, R376.1
unnamed: C372.1, R376.2, R377.1, R378.2
unnamed: C373.2, IC11.6, R377.2
unnamed: Q42.2, R349.2
unnamed: C347.2, C348.2, R353.2, R354.2, R379.1, R380.2
unnamed: C352.1, R355.2
unnamed: C351.1, R355.1, R356.2, R357.2
unnamed: C376.1, IC12.14, R371.1, R382.1
unnamed: C360.2, R364.2
unnamed: C375.1, IC12.13, R382.2
unnamed: C375.2, C376.2, R381.2, R383.2
unnamed: C374.1, R381.1
unnamed: C353.1, C354.1, IC11.8, R357.1
unnamed: C358.2, C359.2, R361.2, R362.2
unnamed: IC11.3, R384.1
unnamed: LED6.ANODE_RED, R344.2
unnamed: LED6.ANODE_GRN, R345.1
unnamed: C381.1, U24.4
RESET: R3.1, SWD.4, U3.26
RESET1: R92.1, SWD1.4, U7.26
RESET2: R156.1, SWD2.4, U11.26
RESET3: R220.1, SWD3.4, U15.26
RESET4: R284.1, SWD4.4, U19.26
RESET5: R348.1, SWD5.4, U23.26
SWDCLK: SWD.3, U3.31
SWDCLK1: SWD1.3, U7.31
SWDCLK2: SWD2.3, U11.31
SWDCLK3: SWD3.3, U15.31
SWDCLK4: SWD4.3, U19.31
SWDCLK5: SWD5.3, U23.31
SWDIO: SWD.2, U3.32
SWDIO1: SWD1.2, U7.32
SWDIO2: SWD2.2, U11.32
SWDIO3: SWD3.2, U15.32
SWDIO4: SWD4.2, U19.32
SWDIO5: SWD5.2, U23.32
USART-RX: C64.1, D5.3, R61.1, U3.18
USART-RX1: C128.1, D8.3, R85.1, U7.18
USART-RX2: C192.1, D13.3, R149.1, U11.18
USART-RX3: C256.1, D18.3, R213.1, U15.18
USART-RX4: C320.1, D23.3, R277.1, U19.18
USART-RX5: C384.1, D28.3, R341.1, U23.18
V+: C6.1, C7.1, C9.1, C10.1, C11.1, C12.1, C25.1, IC1.5, IC1.10, IC1.12, IC2.5, IC2.10, IC2.12, R1.2, R2.2, R16.2, R23.1, R29.2, R36.1, R39.1
V+1: C70.1, C109.1, C110.1, C111.1, C112.1, C123.1, C124.1, IC3.5, IC3.10, IC3.12, IC4.5, IC4.10, IC4.12, R68.2, R106.1, R109.1, R111.2, R112.2, R123.2, R127.1
V+2: C134.1, C173.1, C174.1, C175.1, C176.1, C187.1, C188.1, IC5.5, IC5.10, IC5.12, IC6.5, IC6.10, IC6.12, R132.2, R170.1, R173.1, R175.2, R176.2, R187.2, R191.1
V+3: C198.1, C237.1, C238.1, C239.1, C240.1, C251.1, C252.1, IC7.5, IC7.10, IC7.12, IC8.5, IC8.10, IC8.12, R196.2, R234.1, R237.1, R239.2, R240.2, R251.2, R255.1
V+4: C262.1, C301.1, C302.1, C303.1, C304.1, C315.1, C316.1, IC9.5, IC9.10, IC9.12, IC10.5, IC10.10, IC10.12, R260.2, R298.1, R301.1, R303.2, R304.2, R315.2, R319.1
V+5: C326.1, C365.1, C366.1, C367.1, C368.1, C379.1, C380.1, IC11.5, IC11.10, IC11.12, IC12.5, IC12.10, IC12.12, R324.2, R362.1, R365.1, R367.2, R368.2, R379.2, R383.1
VCC/1: D10.A, VCC1.P$1
VCC/2: D1.A, VCC.P$1
VCC/3: D15.A, VCC2.P$1
VCC/4: D20.A, VCC3.P$1
VCC/5: D25.A, VCC4.P$1
VCC/6: D30.A, VCC5.P$1
XIN: C13.1, QZ1.1, U3.15
XIN1: C122.1, QZ3.1, U7.15
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
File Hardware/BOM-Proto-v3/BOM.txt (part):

Part	Value	Device	Package	Description	ASK	ASK_CUSTOMERPN	ASK_PN	ASK+PSK+MIFARE	ASK+FSK+MIFARE	FSK	FSK_CUSTOMERPN	FSK_PN	MIFARE	MIFARE_CUSTOMERPN	MIFARE_PN	PASSIVO	PN1	PSK	PSK_CUSTOMERPN	PSK_PN	SPECIAL
BZ1	F/TMB	F/TMB	F/TMB	BUZZER Source: Buerklin	X	BUZ-REP	PS1240P02BT	1	1	X	BUZ-REP	PS1240P02BT	X	BUZ-REP	PS1240P02BT			X	BUZ-REP	PS1240P02BT	
C1	4.7u	C-USC0603	C0603	CAPACITOR, American symbol	X	C/4.7u/16V/C06	CL10A475KO8NNNC	1	1	X	C/4.7u/16V/C06	CL10A475KO8NNNC	X	C/4.7u/16V/C06	CL10A475KO8NNNC	Sim		X	C/4.7u/16V/C06	CL10A475KO8NNNC	
C2	ESK108M016AH2AA	ESK108M016AH2AA	ESK108M016AH2AA		X	C/1m/16V/PTH	ESK108M016AH2AA	1	1	X	C/1m/16V/PTH	ESK108M016AH2AA	X	C/1m/16V/PTH	ESK108M016AH2AA	Sim		X	C/1m/16V/PTH	ESK108M016AH2AA	
C3	10n	C-USC0402	C0402	CAPACITOR, American symbol	X	C/10n/50V/C04	CL05B103KB5NNNC	1	1	X	C/10n/50V/C04	CL05B103KB5NNNC	X	C/10n/50V/C04	CL05B103KB5NNNC	Sim		X	C/10n/50V/C04	CL05B103KB5NNNC	
C4	4.7u	C-USC0603	C0603	CAPACITOR, American symbol	X	C/4.7u/16V/C06	CL10A475KO8NNNC	1	1	X	C/4.7u/16V/C06	CL10A475KO8NNNC	X	C/4.7u/16V/C06	CL10A475KO8NNNC	Sim		X	C/4.7u/16V/C06	CL10A475KO8NNNC	
C5	10u	C-USC0805	C0805	CAPACITOR, American symbol	X	C/10u/25V/A08	GRM188R61E106MA73D	1	1	X	C/10u/25V/A08	GRM188R61E106MA73D	X	C/10u/25V/A08	GRM188R61E106MA73D	Sim		X	C/10u/25V/A08	GRM188R61E106MA73D	
C6	0.1u	C-USC0402	C0402	CAPACITOR, American symbol	X	C/0.1u/16V/A04	CL05B104KO5NNNC	1	1	X	C/0.1u/16V/A04	CL05B104KO5NNNC	X	C/0.1u/16V/A04	CL05B104KO5NNNC	Sim		X	C/0.1u/16V/A04	CL05B104KO5NNNC	
C7	10n	C-USC0402	C0402	CAPACITOR, American symbol	X	C/10n/50V/C04	CL05B103KB5NNNC	1	1	X	C/10n/50V/C04	CL05B103KB5NNNC	X	C/10n/50V/C04	CL05B103KB5NNNC	Sim		X	C/10n/50V/C04	CL05B103KB5NNNC	
C8	10u	C-USC0805	C0805	CAPACITOR, American symbol	X	C/10u/25V/A08	GRM188R61E106MA73D	1	1	X	C/10u/25V/A08	GRM188R61E106MA73D	X	C/10u/25V/A08	GRM188R61E106MA73D	Sim		X	C/10u/25V/A08	GRM188R61E106MA73D	
C9	0.1u	C-USC0402	C0402	CAPACITOR, American symbol	X	C/0.1u/16V/A04	CL05B104KO5NNNC	1	1	X	C/0.1u/16V/A04	CL05B104KO5NNNC	X	C/0.1u/16V/A04	CL05B104KO5NNNC	Sim		X	C/0.1u/16V/A04	CL05B104KO5NNNC	
C10	0.1u	C-USC0402	C0402	CAPACITOR, American symbol	X	C/0.1u/16V/A04	CL05B104KO5NNNC	1	1	X	C/0.1u/16V/A04	CL05B104KO5NNNC	X	C/0.1u/16V/A04	CL05B104KO5NNNC	Sim		X	C/0.1u/16V/A04	CL05B104KO5NNNC	
C11	0.1u	C-USC0402	C0402	CAPACITOR, American symbol	X	C/0.1u/16V/A04	CL05B104KO5NNNC	1	1	X	C/0.1u/16V/A04	CL05B104KO5NNNC	X	C/0.1u/16V/A04	CL05B104KO5NNNC	Sim		X	C/0.1u/16V/A04	CL05B104KO5NNNC	
C12	10u	C-USC0805	C0805	CAPACITOR, American symbol	X	C/10u/25V/A08	GRM188R61E106MA73D	1	1	X	C/10u/25V/A08	GRM188R61E106MA73D	X	C/10u/25V/A08	GRM188R61E106MA73D	Sim		X	C/10u/25V/A08	GRM188R61E106MA73D	
C13	18p	C-USC0603	C0603	CAPACITOR, American symbol	X	C/18p/100V/E06	06031U180FAT2A	1	1	X	C/18p/100V/E06	06031U180FAT2A	X	C/18p/100V/E06	06031U180FAT2A	Sim		X	C/18p/100V/E06	06031U180FAT2A	
C14	0.1u	C-USC0402	C0402	CAPACITOR, American symbol	X	C/0.1u/16V/A04	CL05B104KO5NNNC	1	1	X	C/0.1u/16V/A04	CL05B104KO5NNNC	X	C/0.1u/16V/A04	CL05B104KO5NNNC	Sim		X	C/0.1u/16V/A04	CL05B104KO5NNNC	
C15	18p	C-USC0603	C0603	CAPACITOR, American symbol	X	C/18p/100V/E06	06031U180FAT2A	1	1	X	C/18p/100V/E06	06031U180FAT2A	X	C/18p/100V/E06	06031U180FAT2A	Sim		X	C/18p/100V/E06	06031U180FAT2A	
C16	0.1u	C-USC0402	C0402	CAPACITOR, American symbol	X	C/0.1u/16V/A04	CL05B104KO5NNNC	1	1	X	C/0.1u/16V/A04	CL05B104KO5NNNC	X	C/0.1u/16V/A04	CL05B104KO5NNNC	Sim		X	C/0.1u/16V/A04	CL05B104KO5NNNC	
C17	0.1u	C-USC0402	C0402	CAPACITOR, American symbol	X	C/0.1u/16V/A04	CL05B104KO5NNNC	1	1	X	C/0.1u/16V/A04	CL05B104KO5NNNC	X	C/0.1u/16V/A04	CL05B104KO5NNNC	Sim		X	C/0.1u/16V/A04	CL05B104KO5NNNC	
C18	220n	C-USC0402	C0402	CAPACITOR, American symbol	X	C/220n/25V/C04	C1005X5R1E224K050BC	1	1	X	C/220n/25V/C04	C1005X5R1E224K050BC	X	C/220n/25V/C04	C1005X5R1E224K050BC	Sim		X	C/220n/25V/C04	C1005X5R1E224K050BC	
C19	4.7n	C-USC0402	C0402	CAPACITOR, American symbol	X	C/4.7n/25V/D04	CL05B472KA5NNNC	1	1	X	C/4.7n/25V/D04	CL05B472KA5NNNC	X	C/4.7n/25V/D04	CL05B472KA5NNNC	Sim		X	C/4.7n/25V/D04	CL05B472KA5NNNC	
C20	4.7n	C-USC0402	C0402	CAPACITOR, American symbol	X	C/4.7n/25V/D04	CL05B472KA5NNNC	1	1	X	C/4.7n/25V/D04	CL05B472KA5NNNC	X	C/4.7n/25V/D04	CL05B472KA5NNNC	Sim		X	C/4.7n/25V/D04	CL05B472KA5NNNC	
C21	DNP	C-USC0805	C0805	CAPACITOR, American symbol	X	DNP		1	1	X	DNP		X	DNP		Sim		X		DNP	
C22	1n	C-USC1812	C1812	CAPACITOR, American symbol	X	C/1n/500V/E18	C1812C102FBGACTU	1	1	X	C/1n/500V/E18	C1812C102FBGACTU	X	C/1n/500V/E18	C1812C102FBGACTU	Sim		X	C/1n/500V/E18	C1812C102FBGACTU	
C23	68p	C-USC0402	C0402	CAPACITOR, American symbol	X	C/68p/25V/D04	CL05C680JB5NNNC	1	1	X	C/68p/25V/D04	CL05C680JB5NNNC	X	C/68p/25V/D04	CL05C680JB5NNNC	Sim		X	C/68p/25V/D04	CL05C680JB5NNNC	
C24	68p	C-USC0402	C0402	CAPACITOR, American symbol	X	C/68p/25V/D04	CL05C680JB5NNNC	1	1	X	C/68p/25V/D04	CL05C680JB5NNNC	X	C/68p/25V/D04	CL05C680JB5NNNC	Sim		X	C/68p/25V/D04	CL05C680JB5NNNC	
C25	0.1u	C-USC0402	C0402	CAPACITOR, American symbol	X	C/0.1u/16V/A04	CL05B104KO5NNNC	1	1	X	C/0.1u/16V/A04	CL05B104KO5NNNC	X	C/0.1u/16V/A04	CL05B104KO5NNNC	Sim		X	C/0.1u/16V/A04	CL05B104KO5NNNC	
C26	220n	C-USC0402	C0402	CAPACITOR, American symbol	X	C/220n/25V/C04	C1005X5R1E224K050BC	1	1	X	C/220n/25V/C04	C1005X5R1E224K050BC	X	C/220n/25V/C04	C1005X5R1E224K050BC	Sim		X	C/220n/25V/C04	C1005X5R1E224K050BC	
C27	220n	C-USC1206	C1206	CAPACITOR, American symbol	X	C/220n/200V/C12	C3216X7T2E224K160AA	1	1	X	C/220n/200V/C12	C3216X7T2E224K160AA	X	C/220n/200V/C12	C3216X7T2E224K160AA	Sim		X	C/220n/200V/C12	C3216X7T2E224K160AA	
C28	1n	C-USC1206	C1206	CAPACITOR, American symbol	X	C/1n/200V/C12	CL31C102JHHNFNE	1	1	X	C/1n/200V/C12	CL31C102JHHNFNE	X	C/1n/200V/C12	CL31C102JHHNFNE	Sim		X	C/1n/200V/C12	CL31C102JHHNFNE	
C29	F:0.1uP:10n	C-USC0402	C0402	CAPACITOR, American symbol				1	1	X	C/0.1u/16V/A04	CL05B104KO5NNNC				Sim		X	C/10n/50V/C04	CL05B103KB5NNNC	
C30	680p	C-USC0402	C0402	CAPACITOR, American symbol	X	C/680p/25V/C04	CL05B681KB5NNNC	1	1	X	C/680p/25V/C04	CL05B681KB5NNNC	X	C/680p/25V/C04	CL05B681KB5NNNC	Sim		X	C/680p/25V/C04	CL05B681KB5NNNC	
C31	F:220pP:68p	C-USC0402	C0402	CAPACITOR, American symbol				1	1	X	C/220p/25V/D04	CL05C221JB5NNNC				Sim		X	C/68p/25V/D04	CL05C680JB5NNNC	
C32	F:1nP:100p	C-USC0402	C0402	CAPACITOR, American symbol				1	1	X	C/1n/100V/D04	C0402C102J1GACTU				Sim		X	C/100p/50V/D04	CL05C101JB5NNNC	
C33	68p	C-USC0402	C0402	CAPACITOR, American symbol	X	C/68p/25V/D04	CL05C680JB5NNNC	1	1	X	C/68p/25V/D04	CL05C680JB5NNNC	X	C/68p/25V/D04	CL05C680JB5NNNC	Sim		X	C/68p/25V/D04	CL05C680JB5NNNC	
C34	0.1u	C-USC0402	C0402	CAPACITOR, American symbol	X	C/0.1u/16V/A04	CL05B104KO5NNNC	1	1	X	C/0.1u/16V/A04	CL05B104KO5NNNC	X	C/0.1u/16V/A04	CL05B104KO5NNNC	Sim		X	C/0.1u/16V/A04	CL05B104KO5NNNC	
C35	F:0.1uP:10n	C-USC0402	C0402	CAPACITOR, American symbol				1	1	X	C/0.1u/16V/A04	CL05B104KO5NNNC				Sim		X	C/10n/50V/C04	CL05B103KB5NNNC	
C36	47p	C-USC0402	C0402	CAPACITOR, American symbol				1	1	X	C/47p/25V/E04	CL05C470FB5NNNC				Sim		X	C/47p/25V/E04	CL05C470FB5NNNC	
C37	47p	C-USC0402	C0402	CAPACITOR, American symbol				1	1	X	C/47p/25V/E04	CL05C470FB5NNNC				Sim		X	C/47p/25V/E04	CL05C470FB5NNNC	
C38	F:220pP:68p	C-USC0402	C0402	CAPACITOR, American symbol				1	1	X	C/220p/25V/D04	CL05C221JB5NNNC				Sim		X	C/68p/25V/D04	CL05C680JB5NNNC	
C39	F:1nP:100p	C-USC0402	C0402	CAPACITOR, American symbol				1	1	X	C/1n/100V/D04	C0402C102J1GACTU				Sim		X	C/100p/50V/D04	CL05C101JB5NNNC	
C40	47p	C-USC0402	C0402	CAPACITOR, American symbol				1	1	X	C/47p/25V/E04	CL05C470FB5NNNC				Sim		X	C/47p/25V/E04	CL05C470FB5NNNC	
C41	47p	C-USC0402	C0402	CAPACITOR, American symbol				1	1	X	C/47p/25V/E04	CL05C470FB5NNNC				Sim		X	C/47p/25V/E04	CL05C470FB5NNNC	
C42	0.1u	C-USC0402	C0402	CAPACITOR, American symbol	X	C/0.1u/16V/A04	CL05B104KO5NNNC	1	1	X	C/0.1u/16V/A04	CL05B104KO5NNNC	X	C/0.1u/16V/A04	CL05B104KO5NNNC	Sim		X	C/0.1u/16V/A04	CL05B104KO5NNNC	
C43	F:220pP:68p	C-USC0402	C0402	CAPACITOR, American symbol				1	1	X	C/220p/25V/D04	CL05C221JB5NNNC				Sim		X	C/680p/25V/C04	CL05B681KB5NNNC	
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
